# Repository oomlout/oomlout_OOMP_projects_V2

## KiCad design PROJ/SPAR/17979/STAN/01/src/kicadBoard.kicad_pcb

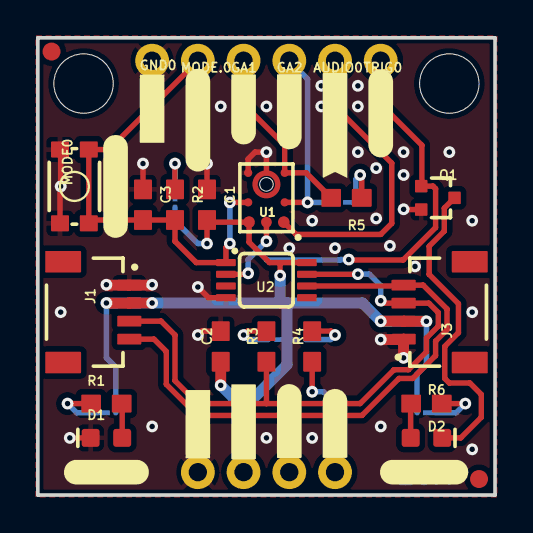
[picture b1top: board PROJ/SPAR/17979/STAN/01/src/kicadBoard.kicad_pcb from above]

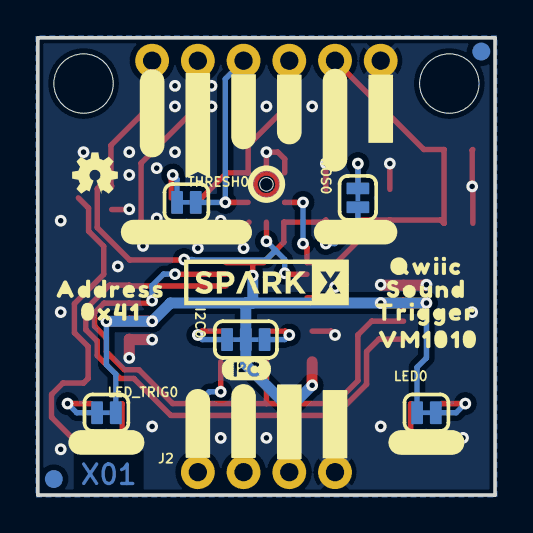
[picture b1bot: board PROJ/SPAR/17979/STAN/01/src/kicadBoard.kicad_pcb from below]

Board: 2 copper layers, 25.4 x 25.4 mm, 74 parts (31 on the bottom side), 18 nets.

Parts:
AUDIO0: 1X01_NO_SILK
C1, C3: 0.1uF; 0603
C2: 1.0uF; 0603
D1, D2: RED; LED-0603
FRAME1: FRAME-LETTER; CREATIVE_COMMONS
GA1, GA2: 1X01_NO_SILK
GND0: 1X01_NO_SILK
I2C0: JUMPER-SMT_3_2-NC_TRACE_SILK; SMT-JUMPER_3_2-NC_TRACE_SILK
J1, J3: Qwiic Right Angle; JST04_1MM_RA
J2: PTH; 1X04_NO_SILK
JP1, JP2, JP5, JP6: FIDUCIAL1X2; FIDUCIAL-1X2
JP3, JP4: STAND-OFF
LED0: SMT-JUMPER_2_NC_TRACE_SILK
LED_TRIG0: SMT-JUMPER_2_NC_TRACE_SILK
LOGO1: OSHW-LOGOMINI; OSHW-LOGO-MINI
LOGO2: SPECIAL_INSTRUCTIONS-ORDERING; ORDERING_INSTRUCTIONS
LOGO3: SPECIAL_INSTRUCTIONS-PRODUCTION; PRODUCTION_INSTRUCTIONS
MODE0: MOMENTARY-SWITCH-SPST-SMD-4.6X2.8MM; TACTILE_SWITCH_SMD_4.6X2.8MM
MODE.0: 1X01_NO_SILK
Q1: 310mA/60V/1.6Ω; SOT323
R1, R6: 1k; 0603
R2, R3, R4: 2.2k; 0603
R5: 20k; 0603
THRESH0: SMT-JUMPER_2_NC_TRACE_SILK
TRIG0: 1X01_NO_SILK
U1: VM1010
U2: PCA9536; MSOP8
U$1, U$3: #GA1#0
U$2: SPARKX-LOGO4; SPARKX-MEDIUM
U$4, U$5: #GA2#0
U$6, U$7: #AUDIO#0
U$8, U$9, U$25: #MODE#0
U$10: I_SUPER2_C-()-03
U$11, U$12, U$35: #TRIG#0
U$13: #PWR#0
U$14, U$36: #LED#0
U$15: #THRESH#0
U$16: #WOS#0
U$17, U$18, U$38, U$39: #GND#0
U$19, U$20: #3#3V#0
U$21, U$22: #SDA#0
U$23, U$24: #SCL#0
U$29: QWIIC0
U$30: SOUND0
U$31: TRIGGER0
U$32: VM10100
U$33: ADDRESS0
U$34: 0X410
WOS0: SMT-JUMPER_2_NC_TRACE_SILK

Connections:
3.3V: C1.1, C2.1, I2C0.2, J1.2, J2.2, J3.2, LED0.2, LED_TRIG0.2, U1.6, U2.8, WOS0.2
AUDIO: AUDIO0.1, U1.1
GA1: GA1.1, R5.1, U1.3
GA2: GA2.1, THRESH0.2, U1.2
GND: C1.2, C2.2, C3.2, D1.C, GND0.1, J1.1, J2.1, J3.1, MODE0.1, MODE0.2, Q1.2, U1.4, U1.8, U2.4
MODE: C3.1, MODE0.3, MODE0.4, MODE.0.1, R2.1, U1.5, U2.1
unnamed: I2C0.1, R4.2
unnamed: I2C0.3, R3.2
unnamed: D1.A, R1.1
unnamed: LED0.1, R1.2
unnamed: R2.2, WOS0.1
unnamed: R5.2, THRESH0.1
unnamed: D2.A, R6.1
unnamed: LED_TRIG0.1, R6.2
unnamed: D2.C, Q1.3
SCL: J1.4, J2.4, J3.4, R4.1, U2.6
SDA: J1.3, J2.3, J3.3, R3.1, U2.7
TRIG: Q1.1, TRIG0.1, U1.7, U2.2

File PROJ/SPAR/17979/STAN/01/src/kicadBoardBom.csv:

"Id";"Designator";"Package";"Quantity";"Designation";"Supplier and ref";
1;"U$13";"#PWR#0";1;"";;;
2;"U2";"MSOP8";1;"PCA9536";;;
3;"MODE0";"TACTILE_SWITCH_SMD_4.6X2.8MM";1;"MOMENTARY-SWITCH-SPST-SMD-4.6X2.8MM";;;
4;"U$6,U$7";"#AUDIO#0";2;"";;;
5;"JP6,JP2,JP5,JP1";"FIDUCIAL-1X2";4;"FIDUCIAL1X2";;;
6;"R6,R1";"0603";2;"1k";;;
7;"U$21,U$22";"#SDA#0";2;"";;;
8;"FRAME1";"CREATIVE_COMMONS";1;"FRAME-LETTER";;;
9;"R4,R2,R3";"0603";3;"2.2k";;;
10;"AUDIO0,MODE.0,GA1,TRIG0,GND0,GA2";"1X01_NO_SILK";6;"";;;
11;"C3,C1";"0603";2;"0.1uF";;;
12;"U$19,U$20";"#3#3V#0";2;"";;;
13;"J1,J3";"JST04_1MM_RA";2;"Qwiic Right Angle";;;
14;"U$8,U$25,U$9";"#MODE#0";3;"";;;
15;"U$39,U$17,U$18,U$38";"#GND#0";4;"";;;
16;"LOGO2";"ORDERING_INSTRUCTIONS";1;"SPECIAL_INSTRUCTIONS-ORDERING";;;
17;"R5";"0603";1;"20k";;;
18;"U$23,U$24";"#SCL#0";2;"";;;
19;"U1";"VM1010";1;"VM1010";;;
20;"U$11,U$35,U$12";"#TRIG#0";3;"";;;
21;"U$1,U$3";"#GA1#0";2;"";;;
22;"JP4,JP3";"STAND-OFF";2;"STAND-OFF";;;
23;"D2,D1";"LED-0603";2;"RED";;;
24;"U$4,U$5";"#GA2#0";2;"";;;
25;"C2";"0603";1;"1.0uF";;;
26;"LOGO3";"PRODUCTION_INSTRUCTIONS";1;"SPECIAL_INSTRUCTIONS-PRODUCTION";;;
27;"Q1";"SOT323";1;"310mA/60V/1.6Ω";;;
28;"U$30";"SOUND0";1;"";;;
29;"U$33";"ADDRESS0";1;"";;;
30;"WOS0,LED_TRIG0,LED0,THRESH0";"SMT-JUMPER_2_NC_TRACE_SILK";4;"";;;
31;"U$15";"#THRESH#0";1;"";;;
32;"U$34";"0X410";1;"";;;
33;"J2";"1X04_NO_SILK";1;"PTH";;;
34;"I2C0";"SMT-JUMPER_3_2-NC_TRACE_SILK";1;"JUMPER-SMT_3_2-NC_TRACE_SILK";;;
35;"U$14,U$36";"#LED#0";2;"";;;
36;"U$16";"#WOS#0";1;"";;;
37;"LOGO1";"OSHW-LOGO-MINI";1;"OSHW-LOGOMINI";;;
38;"U$32";"VM10100";1;"";;;
39;"U$31";"TRIGGER0";1;"";;;
40;"U$29";"QWIIC0";1;"";;;
41;"U$2";"SPARKX-MEDIUM";1;"SPARKX-LOGO4";;;
42;"U$10";"I_SUPER2_C-()-03";1;"";;;

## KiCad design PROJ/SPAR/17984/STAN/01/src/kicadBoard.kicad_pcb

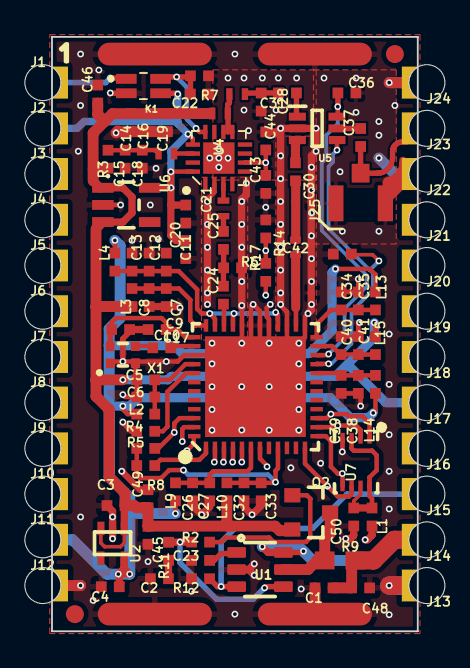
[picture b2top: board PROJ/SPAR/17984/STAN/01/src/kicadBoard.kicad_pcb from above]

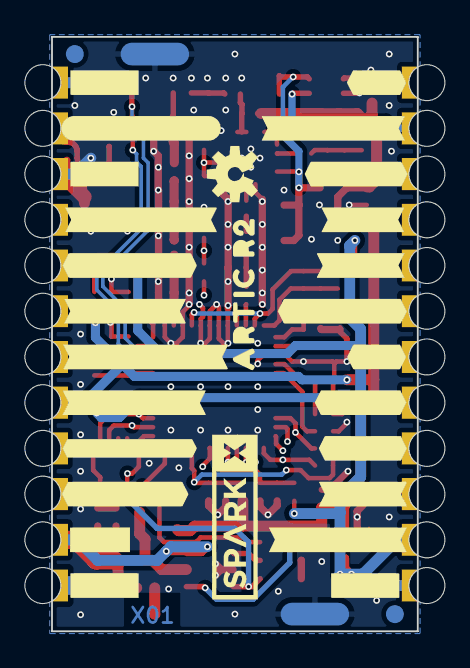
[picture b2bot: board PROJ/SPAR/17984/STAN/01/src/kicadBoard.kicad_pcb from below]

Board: 4 copper layers, 20.3 x 33.0 mm, 146 parts (29 on the bottom side), 57 nets.

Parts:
C1, C15, C16, C20, C44, C45: 2.2uF; 0402-TIGHT
C2: 10nF; 0402-TIGHT
C3, C4, C9, C12, C23, C46: 1.0uF; 0402-TIGHT
C5, C7, C18, C27, C33, C34, C39, C40: 22pF; 0402-TIGHT
C6, C8, C26, C32, C35, C38, C41, C48, C49, C50: 0.1uF; 0402-TIGHT
C10: 47nF; 0402-TIGHT
C11, C19, C21, C22, C24, C25, C30, C31, C36, C37, C42, C43: 100pF; 0402-TIGHT
C13, C14: 10uF; 0402-TIGHT
C17: 1.0nF; 0402-TIGHT
C28: 9.1pF; 0402-TIGHT
C29: 2.4 pF; 0402_MURATA
FD1, FD2, FD3, FD4: FIDUCIAL1X2; FIDUCIAL-1X2
FRAME1: FRAME-LEDGER; CREATIVE_COMMONS
J1, J2, J3, J4, J5, J6, J7, J8, J9, J10, J11, J12, J13, J14, J15, J16, J17, J18, J19, J20, J21, J22, J23, J24: CONN_01_CASTELLATED_4LAYER
J25: U.FL; U.FL_REDUCED_FOOTPRINT
K1: TLP3475R; TLP3475RTPF
L1, L2, L3, L4, L9, L10, L13, L14, L15: 30Ω; 0402-TIGHT
L5: 15nH; 0402_COILCRAFT
L6: 27nH; 0402_COILCRAFT
L7: 18nH; 0402_COILCRAFT
L8: 12nH; 0402_COILCRAFT
L11: 30nH; 0402_COILCRAFT
L12: 51nH; 0402_COILCRAFT
LOGO1: SPECIAL_INSTRUCTIONS-ORDERING; ORDERING_INSTRUCTIONS
LOGO3: OSHW-LOGOS; OSHW-LOGO-S
Q2: 5.8A/30V/35mΩ; SOT23-3
R2, R11: 100; 0402-TIGHT
R3: 3.9; 0402-TIGHT
R4: 33k; 0402-TIGHT
R5, R8: 100k; 0402-TIGHT
R6: 220; 0402-TIGHT
R7, R12: 10k; 0402-TIGHT
R9: 0.1; 0603
R14: 470; 0402-TIGHT
R17: 47; 0402-TIGHT
SCREEN0: IOTA_SCREENING_CANSTRAIGHT_SLOTS; IOTA_CAN_STRAIGHT_SLOTS
SPARKX2: SPARKX-LOGO4; SPARKX-MEDIUM
U1: ADM4210_1TSOT6; TSOT6
U2: 1.8V/100mA; SC70
U3: ARTIC_R2; QFN-48
U4: RFPA0133; QFN50P300X300X86-17N
U5: AS179-92LF; SOT65P220X100-6N
U6: 3.0V; SOT23-5
U7: SST25VF020BUSON; USON_3X2MM
U$1, U$3, U$4, U$5: #GND#0
U$2: 10
U$6: #PWR_EN#0
U$7: #VIN#0
U$8: #FLASH_PWR#0
U$9: #FLSH_SCLK#0
U$10: #FLSH_SI#0
U$11: #FLSH_SO#0
U$12: #FLSH_CEN#0
U$13: #3#3V_OUT#0
U$14: #ANTENNA#0
U$15: #G8#0
U$16: #3#0V_OUT#0
U$17: #BOOT#0
U$18: #INT1#0
U$19: #INT2#0
U$20: #RESETB#0
U$21: #CS#0
U$22: #SCLK#0
U$23: #COPI#0
U$24: #CIPO#0
U$25: #1#8V_OUT#0
U$26: ARTIC_R20
X1: CRYSTAL-TCXO-26MHZ; CRYSTAL-TCXO-SMD-1.65X1.25

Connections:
1.8V: C4.1, J11.1, L2.2, L4.2, L9.2, L13.2, L14.2, U2.5
ANTENNA: C37.1, J23.1, J25.FEED
BOOT: J3.1, R5.1, U3.46
CIPO: J10.1, U3.5
COPI: J9.1, U3.4
CS: J7.1, U3.2
FLASH_PWR: J16.1, L1.2
FLASH_VCC: C50.1, L1.1, U7.3, U7.7, U7.8
FLSH_CEN: J21.1, U3.15, U7.1
FLSH_SCLK: J18.1, U3.12, U7.6
FLSH_SI: J19.1, U3.13, U7.5
FLSH_SO: J20.1, U3.14, U7.2
G8: J1.1, K1.1
GND: C1.2, C2.2, C3.2, C4.2, C5.2, C6.2, C7.2, C8.2, C9.2, C10.2, C11.2, C12.2, C13.2, C14.2, C15.2, C16.2, C18.2, C19.2, C20.1, C21.1, C22.1, C23.2, C26.2, C27.2, C28.1, C32.2, C33.2, C34.2, C35.2, C36.2, C38.2, C39.2, C40.2, C41.2, C42.2, C43.1, C44.2, C45.2, C46.2, C48.2, C49.2, C50.2, J12.1, J13.1, J22.1, J24.1, J25.1, J25.2, K1.2, L11.P$1, L12.P$1, R4.2, R6.1, R7.2, R12.2, R14.1, SCREEN0.1-1, SCREEN0.1-16, SCREEN0.2, SCREEN0.3-1, SCREEN0.3-16, SCREEN0.4, U1.2, U2.2, U3.25, U3.27, U3.29, U3.30, U3.31, U3.32, U3.39, U3.GND, U4.2, U4.EDAP, U5.2, U6.2, U7.4, X1.1, X1.2
INT1: J4.1, U3.47
INT2: J5.1, U3.48
unnamed: Q2.3, R9.1, U1.5
unnamed: Q2.1, R2.1
unnamed: R2.2, R11.1, U1.4
unnamed: C34.1, C35.1, L13.1, U3.24
unnamed: C40.1, C41.1, L15.1, U3.23
unnamed: C2.1, R11.2
unnamed: C23.1, U1.1
unnamed: C26.1, C27.1, L9.1, U3.6
unnamed: C32.1, C33.1, L10.1, R5.2, R8.1, U3.9
unnamed: C11.1, C12.1, C13.1, L4.1, U3.28, U3.33, U3.35
unnamed: C7.1, C8.1, L3.1, U3.36
unnamed: R4.1, U3.41
unnamed: C5.1, C6.1, L2.1, U3.40
unnamed: C9.1, C10.1, U3.37, X1.4
unnamed: C17.1, X1.3
unnamed: C17.2, U3.38
unnamed: C24.1, U3.34
unnamed: C24.2, C25.1, R6.2
unnamed: L5.P$2, U4.14
unnamed: C15.1, C18.1, L5.P$1, R3.1
unnamed: C29.P$1, L11.P$2, U3.26
unnamed: C25.2, L7.P$1
unnamed: L7.P$2, U4.3
unnamed: L6.P$2, L8.P$1, U4.9, U4.10
unnamed: C31.1, U5.1
unnamed: C30.1, U5.3
unnamed: C37.2, U5.5
unnamed: C38.1, C39.1, L14.1, U3.20
PA_PD: R17.1, U3.7
PD: C43.2, C44.1, R14.2, R17.2, U4.6
PWR_EN: J15.1, R12.1, U1.3
RESETB: J6.1, R8.2, U3.1
RFG8: C22.2, K1.4, R7.1, U4.12
RF_RX: C29.P$2, C30.2, L12.P$2
RF_TX: C28.2, C31.2, L8.P$2
RXSW: C36.1, U3.22, U5.6
SCLK: J8.1, U3.3
TXSW: C42.1, U3.21, U5.4
VDD: C3.1, C14.1, C16.1, C19.1, C45.1, C46.1, C49.1, J17.1, L3.2, L6.P$1, L10.2, L15.2, Q2.2, R3.2, U2.1, U2.3, U6.1, U6.3
VIN: C1.1, C48.1, J14.1, R9.2, U1.6
VREF1: C20.2, C21.2, J2.1, K1.3, U4.13, U4.16, U6.5

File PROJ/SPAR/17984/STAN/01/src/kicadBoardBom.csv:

"Id";"Designator";"Package";"Quantity";"Designation";"Supplier and ref";
1;"J20,J18,J9,J11,J10,J2,J6,J17,J1,J16,J5,J19,J24,J15,J4,J23,J13,J8,J22,J3,J14,J12,J7,J21";"CONN_01_CASTELLATED_4LAYER";24;"";;;
2;"C18,C27,C33,C5,C34,C39,C40,C7";"0402-TIGHT";8;"22pF";;;
3;"R4";"0402-TIGHT";1;"33k";;;
4;"K1";"TLP3475RTPF";1;"TLP3475R";;;
5;"C43,C42,C21,C37,C11,C31,C25,C19,C30,C22,C36,C24";"0402-TIGHT";12;"100pF";;;
6;"C29";"0402_MURATA";1;"2.4 pF";;;
7;"C13,C14";"0402-TIGHT";2;"10uF";;;
8;"C4,C9,C12,C46,C23,C3";"0402-TIGHT";6;"1.0uF";;;
9;"L6";"0402_COILCRAFT";1;"27nH";;;
10;"C1,C20,C44,C45,C16,C15";"0402-TIGHT";6;"2.2uF";;;
11;"FD1,FD3,FD4,FD2";"FIDUCIAL-1X2";4;"FIDUCIAL1X2";;;
12;"L10,L14,L9,L13,L3,L15,L1,L4,L2";"0402-TIGHT";9;"30Ω";;;
13;"L7";"0402_COILCRAFT";1;"18nH";;;
14;"R14";"0402-TIGHT";1;"470";;;
15;"C2";"0402-TIGHT";1;"10nF";;;
16;"Q2";"SOT23-3";1;"5.8A/30V/35mΩ";;;
17;"R8,R5";"0402-TIGHT";2;"100k";;;
18;"R3";"0402-TIGHT";1;"3.9";;;
19;"L5";"0402_COILCRAFT";1;"15nH";;;
20;"C8,C50,C32,C35,C38,C49,C41,C48,C26,C6";"0402-TIGHT";10;"0.1uF";;;
21;"R12,R7";"0402-TIGHT";2;"10k";;;
22;"U5";"SOT65P220X100-6N";1;"AS179-92LF";;;
23;"U4";"QFN50P300X300X86-17N";1;"RFPA0133";;;
24;"X1";"CRYSTAL-TCXO-SMD-1.65X1.25";1;"CRYSTAL-TCXO-26MHZ";;;
25;"U2";"SC70";1;"1.8V/100mA";;;
26;"R11,R2";"0402-TIGHT";2;"100";;;
27;"L11";"0402_COILCRAFT";1;"30nH";;;
28;"SCREEN0";"IOTA_CAN_STRAIGHT_SLOTS";1;"IOTA_SCREENING_CANSTRAIGHT_SLOTS";;;
29;"U7";"USON_3X2MM";1;"SST25VF020BUSON";;;
30;"U1";"TSOT6";1;"ADM4210_1TSOT6";;;
31;"C10";"0402-TIGHT";1;"47nF";;;
32;"L8";"0402_COILCRAFT";1;"12nH";;;
33;"LOGO1";"ORDERING_INSTRUCTIONS";1;"SPECIAL_INSTRUCTIONS-ORDERING";;;
34;"U$2";"10";1;"";;;
35;"J25";"U.FL_REDUCED_FOOTPRINT";1;"U.FL";;;
36;"R6";"0402-TIGHT";1;"220";;;
37;"C17";"0402-TIGHT";1;"1.0nF";;;
38;"C28";"0402-TIGHT";1;"9.1pF";;;
39;"R17";"0402-TIGHT";1;"47";;;
40;"U3";"QFN-48";1;"ARTIC_R2";;;
41;"L12";"0402_COILCRAFT";1;"51nH";;;
42;"U6";"SOT23-5";1;"3.0V";;;
43;"FRAME1";"CREATIVE_COMMONS";1;"FRAME-LEDGER";;;
44;"R9";"0603";1;"0.1";;;
45;"U$14";"#ANTENNA#0";1;"";;;
46;"U$21";"#CS#0";1;"";;;
47;"U$7";"#VIN#0";1;"";;;
48;"U$22";"#SCLK#0";1;"";;;
49;"LOGO3";"OSHW-LOGO-S";1;"OSHW-LOGOS";;;
50;"U$3,U$4,U$5,U$1";"#GND#0";4;"";;;
51;"U$8";"#FLASH_PWR#0";1;"";;;
52;"U$6";"#PWR_EN#0";1;"";;;
53;"U$12";"#FLSH_CEN#0";1;"";;;
54;"U$26";"ARTIC_R20";1;"";;;
55;"U$24";"#CIPO#0";1;"";;;
56;"U$16";"#3#0V_OUT#0";1;"";;;
57;"U$20";"#RESETB#0";1;"";;;
58;"U$23";"#COPI#0";1;"";;;
59;"U$11";"#FLSH_SO#0";1;"";;;
60;"U$13";"#3#3V_OUT#0";1;"";;;
61;"U$18";"#INT1#0";1;"";;;
62;"U$10";"#FLSH_SI#0";1;"";;;
63;"U$9";"#FLSH_SCLK#0";1;"";;;
64;"U$25";"#1#8V_OUT#0";1;"";;;
65;"U$19";"#INT2#0";1;"";;;
66;"U$17";"#BOOT#0";1;"";;;
67;"U$15";"#G8#0";1;"";;;
68;"SPARKX2";"SPARKX-MEDIUM";1;"SPARKX-LOGO4";;;

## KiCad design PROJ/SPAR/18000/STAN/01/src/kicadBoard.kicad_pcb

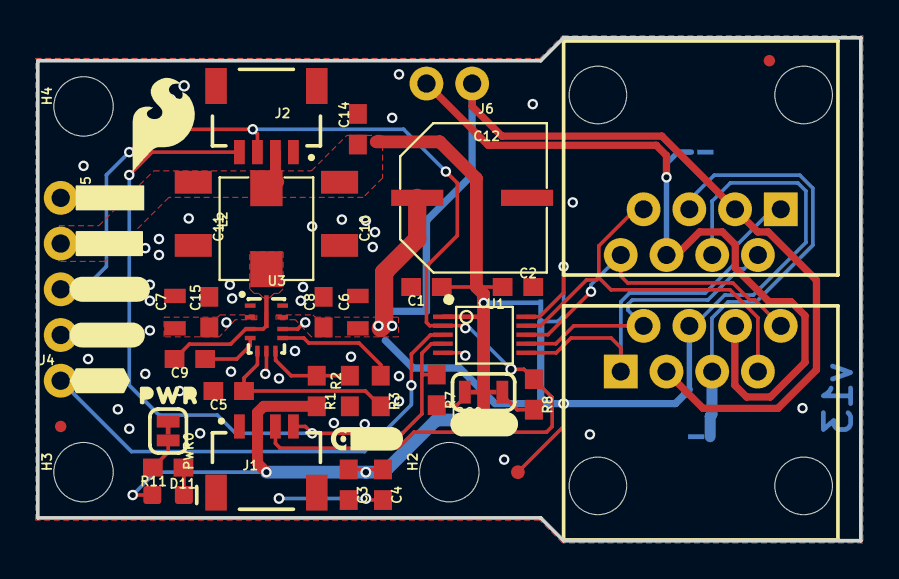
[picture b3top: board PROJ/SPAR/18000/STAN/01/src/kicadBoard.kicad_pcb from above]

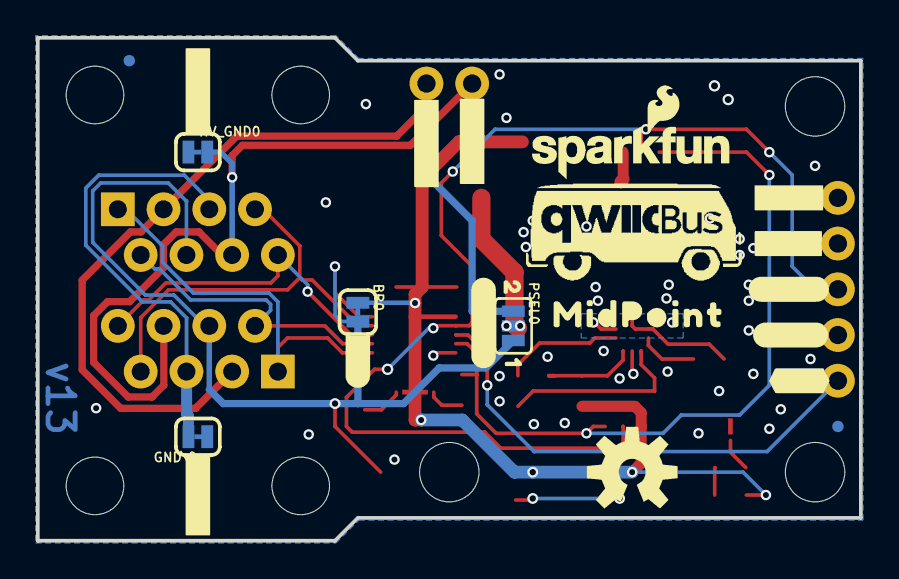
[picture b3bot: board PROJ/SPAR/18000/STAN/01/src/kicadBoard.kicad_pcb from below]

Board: 2 copper layers, 45.7 x 27.9 mm, 73 parts (23 on the bottom side), 23 nets.

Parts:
BP0: JUMPER-SMT_2_NC_TRACE_SILK; SMT-JUMPER_2_NC_TRACE_SILK
C1, C2, C9, C14: 0.1uF; 0603
C3, C4, C5: 1.0uF; 0603
C6, C7: 4.7uF; 0805
C8, C15: 0.22uF; 0603
C10, C11: 22uF; 1210
C12: 100uF; 8X10.5
D11: RED; LED-0603
FD1, FD2, FD3, FD4: FIDUCIALUFIDUCIAL; FIDUCIAL-MICRO
FRAME1: FRAME-LETTER; CREATIVE_COMMONS
GND\0: JUMPER-SMT_2_NC_TRACE_SILK; SMT-JUMPER_2_NC_TRACE_SILK
H2, H3, H4: STAND-OFF
HV_GND0: JUMPER-SMT_2_NC_TRACE_SILK; SMT-JUMPER_2_NC_TRACE_SILK
I2C0: JUMPER-SMT_3_2-NC_TRACE_SILK; SMT-JUMPER_3_2-NC_TRACE_SILK
J1, J2: QWIIC; JST04_1MM_RA
J3, J7: RJ45; RJ45-8
J4: 1X01_NO_SILK
J5: 1X04_NO_SILK
J6: 1X02_NO_SILK
L2: 2.2uH; INDUCTOR_5X5MM
LOGO1: OSHW-LOGOM; OSHW-LOGO-M
LOGO3: SFE_LOGO_FLAME.2_INCH; SFE_LOGO_FLAME_.2
LOGO4: SFE_LOGO_NAME_FLAME.1_INCH; SFE_LOGO_NAME_FLAME_.1
PSEL0: JUMPER-SMT_3_NO_SILK; SMT-JUMPER_3_NO_SILK
PWR0: JUMPER-SMT_2_NC_TRACE_SILK; SMT-JUMPER_2_NC_TRACE_SILK
R1, R3: 100k; 0603
R2: 43k; 0603
R7, R8: 4.7k; 0603
R11: 1k; 0603
TP1: TEST-POINT3; PAD.03X.03
U1: PCA9615; TSSOP10
U3: LMR33630; VQFN-HR-12
U$1, U$7: #GND#0
U$2, U$8: #3V3#0
U$3, U$9: #SDA#0
U$4, U$10: #SCL#0
U$5: #BP#0
U$6, U$12: #EN#0
U$11, U$24: #GND2#0
U$13: #I2C#0
U$14: #GND1#0
U$15: QWIICBUS#WORKING#LOGO#JPG
U$16: #VCC2#0
U$17: #PSEL#0
U$18: 10
U$19: 20
U$20: ORDERING_INSTRUCTIONS
U$22: QWIIC_4MM
U$23: PWR0
U$30: MIDPOINT0

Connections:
3.3V: BP0.1, C1.1, C2.1, C3.1, C4.1, C10.1, C11.1, C14.1, D11.A, I2C0.2, J1.2, J2.2, J5.2, L2.P$2, R1.2, U1.1
BLUE_N: GND\0.2, J3.5, J7.5
DSCL_N: J3.1, J7.1, U1.6
DSCL_P: J3.2, J7.2, U1.7
DSDA_N: J3.7, J7.7, U1.9
DSDA_P: J3.8, J7.8, U1.8
EN: J4.1, U1.3
GND: C1.2, C2.2, C3.2, C4.2, C5.2, C6.2, C7.2, C8.2, C10.2, C11.2, C12.-, C14.2, C15.2, GND\0.1, HV_GND0.1, J1.1, J2.1, J5.1, PWR0.1, R2.1, U1.5, U3.1, U3.6, U3.11
GRN_N: HV_GND0.2, J3.6, J6.2, J7.6
unnamed: C9.1, U3.4
unnamed: I2C0.1, R8.2
unnamed: I2C0.3, R7.2
unnamed: R1.1, R2.2, U3.7
unnamed: R3.1, U3.8
unnamed: C5.1, R3.2, U3.5
unnamed: D11.C, R11.1
unnamed: PWR0.2, R11.2
SCL: J1.4, J2.4, J5.4, R7.1, U1.4
SDA: J1.3, J2.3, J5.3, R8.1, U1.2
SW: C9.2, L2.P$1, U3.3, U3.12
VCC_1: BP0.2, J3.4, J7.4, PSEL0.3, TP1.P$1, U1.10
VCC_2: J3.3, J6.1, J7.3, PSEL0.1
VREG_IN: C6.1, C7.1, C8.1, C12.+, C15.1, PSEL0.2, U3.2, U3.9, U3.10

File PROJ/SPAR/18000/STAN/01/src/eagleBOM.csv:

"Part";"Value";"Device";"Package";"Description";"DESIGNER";"PROD_ID";"REV";"SF_ID";"VALUE";
"BP";"JUMPER-SMT_2_NC_TRACE_SILK";"JUMPER-SMT_2_NC_TRACE_SILK";"SMT-JUMPER_2_NC_TRACE_SILK";"Normally closed trace jumper";"";"";"";"";"";
"C1";"0.1uF";"0.1UF-0603-25V-(+80/-20%)";"0603";"0.1µF ceramic capacitors";"";"CAP-00810";"";"";"0.1uF";
"C2";"0.1uF";"0.1UF-0603-25V-(+80/-20%)";"0603";"0.1µF ceramic capacitors";"";"CAP-00810";"";"";"0.1uF";
"C3";"1.0uF";"1.0UF-0603-16V-10%";"0603";"1µF ceramic capacitors";"";"CAP-00868";"";"";"1.0uF";
"C4";"1.0uF";"1.0UF-0603-16V-10%";"0603";"1µF ceramic capacitors";"";"CAP-00868";"";"";"1.0uF";
"C5";"1.0uF";"1.0UF-0603-16V-10%";"0603";"1µF ceramic capacitors";"";"CAP-00868";"";"";"1.0uF";
"C6";"4.7uF";"4.7UF-0805-50V-(10%)";"0805";"4.7µF ceramic capacitors";"";"CAP-15457";"";"";"4.7uF";
"C7";"4.7uF";"4.7UF-0805-50V-(10%)";"0805";"4.7µF ceramic capacitors";"";"CAP-15457";"";"";"4.7uF";
"C8";"0.22uF";"0.22UF-0603-50V-10%";"0603";"0.22µF ceramic capacitors";"";"CAP-15456";"";"";"0.22uF";
"C9";"0.1uF";"0.1UF-0603-100V-10%";"0603";"0.1µF ceramic capacitors";"";"CAP-08390";"";"";"0.1uF";
"C10";"22uF";"22UF-1210-16V-20%";"1210";"22µF ceramic capacitors";"";"CAP-10381";"";"";"22uF";
"C11";"22uF";"22UF-1210-16V-20%";"1210";"22µF ceramic capacitors";"";"CAP-10381";"";"";"22uF";
"C12";"100uF";"100UF-POLAR-8X10.5-50V";"8X10.5";"100µF polarized capacitors";"";"CAP-15455";"";"";"100uF";
"C14";"0.1uF";"0.1UF-0603-100V-10%";"0603";"0.1µF ceramic capacitors";"";"CAP-08390";"";"";"0.1uF";
"C15";"0.22uF";"0.22UF-0603-50V-10%";"0603";"0.22µF ceramic capacitors";"";"CAP-15456";"";"";"0.22uF";
"D11";"RED";"LED-RED0603";"LED-0603";"Red SMD LED";"";"DIO-00819";"";"";"RED";
"FD1";"FIDUCIALUFIDUCIAL";"FIDUCIALUFIDUCIAL";"FIDUCIAL-MICRO";"Fiducial Alignment Points";"";"";"";"";"";
"FD2";"FIDUCIALUFIDUCIAL";"FIDUCIALUFIDUCIAL";"FIDUCIAL-MICRO";"Fiducial Alignment Points";"";"";"";"";"";
"FD3";"FIDUCIALUFIDUCIAL";"FIDUCIALUFIDUCIAL";"FIDUCIAL-MICRO";"Fiducial Alignment Points";"";"";"";"";"";
"FD4";"FIDUCIALUFIDUCIAL";"FIDUCIALUFIDUCIAL";"FIDUCIAL-MICRO";"Fiducial Alignment Points";"";"";"";"";"";
"FRAME1";"FRAME-LETTER";"FRAME-LETTER";"CREATIVE_COMMONS";"Schematic Frame - Letter";"";"";"";"";"";
"GND\";"JUMPER-SMT_2_NC_TRACE_SILK";"JUMPER-SMT_2_NC_TRACE_SILK";"SMT-JUMPER_2_NC_TRACE_SILK";"Normally closed trace jumper";"";"";"";"";"";
"H2";"STAND-OFF";"STAND-OFF";"STAND-OFF";"Stand Off";"";"";"";"";"";
"H3";"STAND-OFF";"STAND-OFF";"STAND-OFF";"Stand Off";"";"";"";"";"";
"H4";"STAND-OFF";"STAND-OFF";"STAND-OFF";"Stand Off";"";"";"";"";"";
"HV_GND";"JUMPER-SMT_2_NC_TRACE_SILK";"JUMPER-SMT_2_NC_TRACE_SILK";"SMT-JUMPER_2_NC_TRACE_SILK";"Normally closed trace jumper";"";"";"";"";"";
"I2C";"JUMPER-SMT_3_2-NC_TRACE_SILK";"JUMPER-SMT_3_2-NC_TRACE_SILK";"SMT-JUMPER_3_2-NC_TRACE_SILK";"Normally closed trace jumper (2 of 2 connections)";"";"";"";"";"";
"J1";"QWIIC";"QWIIC_CONNECTORJS-1MM";"JST04_1MM_RA";"SparkFun I2C Standard Qwiic Connector";"";"CONN-13694";"";"";"QWIIC_RIGHT_ANGLE";
"J2";"QWIIC";"QWIIC_CONNECTORJS-1MM";"JST04_1MM_RA";"SparkFun I2C Standard Qwiic Connector";"";"CONN-13694";"";"";"QWIIC_RIGHT_ANGLE";
"J3";"RJ45";"RJ45-8";"RJ45-8";"RJ45 Jack - 8 pin";"";"CONN-08506";"";"PRT-00643";"RJ45";
"J4";"";"CONN_01PTH_NO_SILK_YES_STOP";"1X01_NO_SILK";"Single connection point. Often used as Generic Header-pin footprint for 0.1 inch spaced/style header connections";"";"";"";"";"";
"J5";"";"CONN_041X04_NO_SILK";"1X04_NO_SILK";"Multi connection point. Often used as Generic Header-pin footprint for 0.1 inch spaced/style header connections";"";"CONN-09696";"";"";"";
"J6";"";"CONN_021X02_NO_SILK";"1X02_NO_SILK";"Multi connection point. Often used as Generic Header-pin footprint for 0.1 inch spaced/style header connections";"";"";"";"";"";
"J7";"RJ45";"RJ45-8";"RJ45-8";"RJ45 Jack - 8 pin";"";"CONN-08506";"";"PRT-00643";"RJ45";
"L2";"2.2uH";"2.2μH_SHIELDED_INDUCTOR_5X5";"INDUCTOR_5X5MM";"Murata 2.2uH Inductor";"";"NDUC-15453";"";"";"2.2uH";
"LOGO1";"OSHW-LOGOM";"OSHW-LOGOM";"OSHW-LOGO-M";"Open-Source Hardware (OSHW) Logo";"";"";"";"";"";
"LOGO3";"SFE_LOGO_FLAME.2_INCH";"SFE_LOGO_FLAME.2_INCH";"SFE_LOGO_FLAME_.2";"SparkFun Flame Logo";"";"";"";"";"";
"LOGO4";"SFE_LOGO_NAME_FLAME.1_INCH";"SFE_LOGO_NAME_FLAME.1_INCH";"SFE_LOGO_NAME_FLAME_.1";"SparkFun Font Logo w/ Flame";"";"";"";"";"";
"PSEL";"JUMPER-SMT_3_NO_SILK";"JUMPER-SMT_3_NO_SILK";"SMT-JUMPER_3_NO_SILK";"Normally open jumper";"";"";"";"";"";
"PWR";"JUMPER-SMT_2_NC_TRACE_SILK";"JUMPER-SMT_2_NC_TRACE_SILK";"SMT-JUMPER_2_NC_TRACE_SILK";"Normally closed trace jumper";"";"";"";"";"";
"R1";"100k";"100KOHM-0603-1/10W-1%";"0603";"100kΩ resistor";"";"RES-07828";"";"";"100k";
"R2";"43k";"43KOHM-0603-1/10W-1%";"0603";"43kΩ resistor";"";"RES-07858";"";"";"43k";
"R3";"100k";"100KOHM-0603-1/10W-1%";"0603";"100kΩ resistor";"";"RES-07828";"";"";"100k";
"R7";"4.7k";"4.7KOHM-0603-1/10W-1%";"0603";"4.7kΩ resistor";"";"RES-07857";"";"";"4.7k";
"R8";"4.7k";"4.7KOHM-0603-1/10W-1%";"0603";"4.7kΩ resistor";"";"RES-07857";"";"";"4.7k";
"R11";"1k";"1KOHM-0603-1/10W-1%";"0603";"1kΩ resistor";"";"RES-07856";"";"";"1k";
"TP1";"TEST-POINT3";"TEST-POINT3";"PAD.03X.03";"SparkFun Test Points";"";"";"";"";"";
"U1";"PCA9615";"PCA9615";"TSSOP10";"Differential I2C Bus Buffer";"";"IC-13899";"";"";"";
"U3";"LMR33630";"LMR33630";"VQFN-HR-12";"Texas Instruments LMR33630 3.8V-36V 3A Regulator";"";"VREG-15445";"";"";"LMR33630";

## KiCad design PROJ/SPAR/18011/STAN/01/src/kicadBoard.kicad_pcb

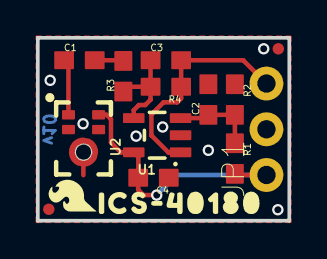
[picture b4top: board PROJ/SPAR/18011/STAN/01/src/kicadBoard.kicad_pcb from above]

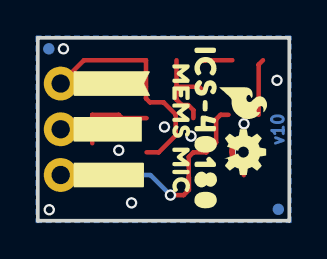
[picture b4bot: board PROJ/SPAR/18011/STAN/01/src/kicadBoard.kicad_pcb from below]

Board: 2 copper layers, 14.0 x 10.2 mm, 25 parts (9 on the bottom side), 7 nets.

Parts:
C1: 4.7uF; 0603
C2: 1.0uF; 0603
C3: 27pF; 0603
C4: 0.1uF; 0603
FD1, FD2, FD3, FD4: FIDUCIALUFIDUCIAL; FIDUCIAL-MICRO
FRAME2: FRAME-LETTER; CREATIVE_COMMONS
JP1: 1X03_NO_SILK
LOGO1, LOGO3: SFE_LOGO_FLAME.1_INCH; SFE_LOGO_FLAME_.1
LOGO2: OSHW-LOGOMINI; OSHW-LOGO-MINI
R1, R2: 10k; 0603
R3: 4.7k; 0603
R4: 300k; 0603
U1: OPA344; SOT23-5
U2: ICS40180
U$1, U$6: ICS#401800
U$2: MEMS_MIC0
U$3: #GND#0
U$4: #VCC#0
U$5: #AUD#0

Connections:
AUD: C3.2, JP1.3, R4.1, U1.1
GND: C2.2, C4.1, JP1.2, R2.1, U1.2, U2.2, U2.3, U2.4
unnamed: C1.1, U2.1
unnamed: C3.1, R3.1, R4.2, U1.4
unnamed: C1.2, R3.2
unnamed: C2.1, R1.1, R2.2, U1.3
VCC: C4.2, JP1.1, R1.2, U1.5, U2.5

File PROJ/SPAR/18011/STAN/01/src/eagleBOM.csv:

"Part";"Value";"Device";"Package";"Description";"DESIGNER";"PROD_ID";"REV";"VALUE";
"C1";"4.7uF";"4.7UF-0603-6.3V-(10%)";"0603";"4.7µF ceramic capacitors";"";"CAP-08280";"";"4.7uF";
"C2";"1.0uF";"1.0UF-0603-16V-10%";"0603";"1µF ceramic capacitors";"";"CAP-00868";"";"1.0uF";
"C3";"27pF";"27PF-0603-50V-5%";"0603";"27pF ceramic capacitors";"";"CAP-09989";"";"27pF";
"C4";"0.1uF";"0.1UF-0603-25V-(+80/-20%)";"0603";"0.1µF ceramic capacitors";"";"CAP-00810";"";"0.1uF";
"FD1";"FIDUCIALUFIDUCIAL";"FIDUCIALUFIDUCIAL";"FIDUCIAL-MICRO";"Fiducial Alignment Points";"";"";"";"";
"FD2";"FIDUCIALUFIDUCIAL";"FIDUCIALUFIDUCIAL";"FIDUCIAL-MICRO";"Fiducial Alignment Points";"";"";"";"";
"FD3";"FIDUCIALUFIDUCIAL";"FIDUCIALUFIDUCIAL";"FIDUCIAL-MICRO";"Fiducial Alignment Points";"";"";"";"";
"FD4";"FIDUCIALUFIDUCIAL";"FIDUCIALUFIDUCIAL";"FIDUCIAL-MICRO";"Fiducial Alignment Points";"";"";"";"";
"FRAME2";"FRAME-LETTER";"FRAME-LETTER";"CREATIVE_COMMONS";"Schematic Frame - Letter";"";"";"";"";
"JP1";"";"CONN_031X03_NO_SILK";"1X03_NO_SILK";"Multi connection point. Often used as Generic Header-pin footprint for 0.1 inch spaced/style header connections";"";"";"";"";
"LOGO1";"SFE_LOGO_FLAME.1_INCH";"SFE_LOGO_FLAME.1_INCH";"SFE_LOGO_FLAME_.1";"SparkFun Flame Logo";"";"";"";"";
"LOGO2";"OSHW-LOGOMINI";"OSHW-LOGOMINI";"OSHW-LOGO-MINI";"Open-Source Hardware (OSHW) Logo";"";"";"";"";
"R1";"10k";"10KOHM-0603-1/10W-1%";"0603";"10kΩ resistor";"";"RES-00824";"";"10k";
"R2";"10k";"10KOHM-0603-1/10W-1%";"0603";"10kΩ resistor";"";"RES-00824";"";"10k";
"R3";"4.7k";"4.7KOHM-0603-1/10W-1%";"0603";"4.7kΩ resistor";"";"RES-07857";"";"4.7k";
"R4";"300k";"300KOHM-0603-1/10W-1%";"0603";"300kΩ resistor";"";"RES-10809";"";"300k";
"U1";"OPA344";"OPA344";"SOT23-5";"Single gate rail-to-rail output op-amp. Inputs extend 300mV past rails.";"";"IC-08251";"";"OPA344";
"U2";"ICS40180";"ICS40180";"ICS40180";"ICS-40180 - RF-Hardened, Low-Noise MEMs Microphone with Bottom Port and Analog Output";"";"IC-15819";"";"";

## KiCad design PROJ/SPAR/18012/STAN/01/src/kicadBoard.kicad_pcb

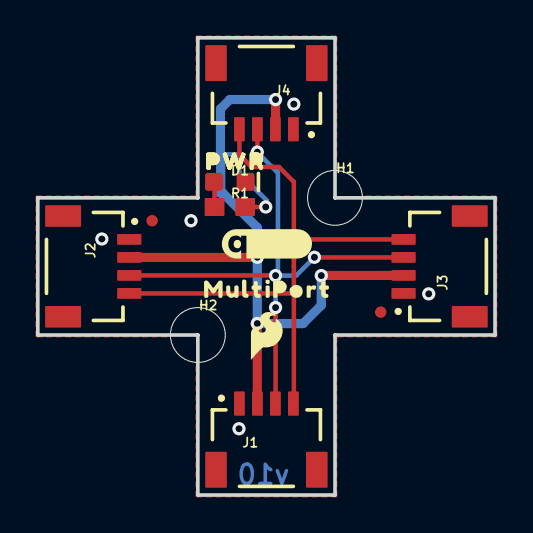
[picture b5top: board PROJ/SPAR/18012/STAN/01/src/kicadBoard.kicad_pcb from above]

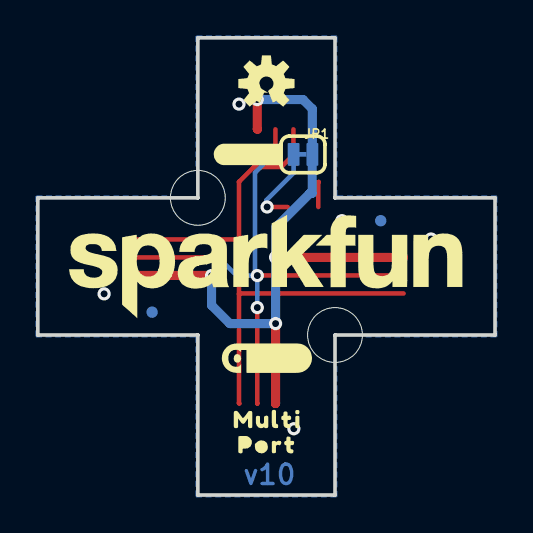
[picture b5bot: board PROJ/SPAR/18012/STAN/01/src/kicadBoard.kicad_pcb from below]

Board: 2 copper layers, 25.4 x 25.4 mm, 25 parts (9 on the bottom side), 6 nets.

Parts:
D1: RED; LED-0603
FD1, FD2, FD3, FD4: FIDUCIALUFIDUCIAL; FIDUCIAL-MICRO
FRAME1: FRAME-LETTER; CREATIVE_COMMONS
H1, H2: STAND-OFFTIGHT; STAND-OFF-TIGHT
J1, J2, J3, J4: QWIIC_RIGHT_ANGLE; JST04_1MM_RA
JP1: PWR_LED; SMT-JUMPER_2_NC_TRACE_SILK
LOGO1, LOGO2: QWIIC_LOGO_5MM; QWIIC_5MM
LOGO3: OSHW-LOGOS; OSHW-LOGO-S
LOGO4: SFE_LOGO_NAME.2_INCH; SFE_LOGO_NAME_.2
R1: 1k; 0603
U$1, U$9: PWR0
U$2: SFE_LOGO_FLAME_.1
U$4: MULTIPORT0
U$5: #PWR#0
U$11: MULTI0
U$13: PORT0

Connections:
3.3V: J1.2, J2.2, J3.2, J4.2, JP1.2
GND: D1.C, J1.1, J2.1, J3.1, J4.1
unnamed: D1.A, R1.1
unnamed: JP1.1, R1.2
SCL: J1.4, J2.4, J3.4, J4.4
SDA: J1.3, J2.3, J3.3, J4.3

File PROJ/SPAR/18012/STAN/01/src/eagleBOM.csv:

"Part";"Value";"Device";"Package";"Description";"DESIGNER";"PROD_ID";"REV";"VALUE";
"D1";"RED";"LED-RED0603";"LED-0603";"Red SMD LED";"";"DIO-00819";"";"RED";
"FD1";"FIDUCIALUFIDUCIAL";"FIDUCIALUFIDUCIAL";"FIDUCIAL-MICRO";"Fiducial Alignment Points";"";"";"";"";
"FD2";"FIDUCIALUFIDUCIAL";"FIDUCIALUFIDUCIAL";"FIDUCIAL-MICRO";"Fiducial Alignment Points";"";"";"";"";
"FD3";"FIDUCIALUFIDUCIAL";"FIDUCIALUFIDUCIAL";"FIDUCIAL-MICRO";"Fiducial Alignment Points";"";"";"";"";
"FD4";"FIDUCIALUFIDUCIAL";"FIDUCIALUFIDUCIAL";"FIDUCIAL-MICRO";"Fiducial Alignment Points";"";"";"";"";
"FRAME1";"FRAME-LETTER";"FRAME-LETTER";"CREATIVE_COMMONS";"Schematic Frame - Letter";"";"";"";"";
"H1";"STAND-OFFTIGHT";"STAND-OFFTIGHT";"STAND-OFF-TIGHT";"Stand Off";"";"";"";"";
"H2";"STAND-OFFTIGHT";"STAND-OFFTIGHT";"STAND-OFF-TIGHT";"Stand Off";"";"";"";"";
"J1";"QWIIC_RIGHT_ANGLE";"QWIIC_CONNECTORJS-1MM";"JST04_1MM_RA";"SparkFun I2C Standard Qwiic Connector";"";"CONN-13694";"";"QWIIC_RIGHT_ANGLE";
"J2";"QWIIC_RIGHT_ANGLE";"QWIIC_CONNECTORJS-1MM";"JST04_1MM_RA";"SparkFun I2C Standard Qwiic Connector";"";"CONN-13694";"";"QWIIC_RIGHT_ANGLE";
"J3";"QWIIC_RIGHT_ANGLE";"QWIIC_CONNECTORJS-1MM";"JST04_1MM_RA";"SparkFun I2C Standard Qwiic Connector";"";"CONN-13694";"";"QWIIC_RIGHT_ANGLE";
"J4";"QWIIC_RIGHT_ANGLE";"QWIIC_CONNECTORJS-1MM";"JST04_1MM_RA";"SparkFun I2C Standard Qwiic Connector";"";"CONN-13694";"";"QWIIC_RIGHT_ANGLE";
"JP1";"PWR_LED";"JUMPER-SMT_2_NC_TRACE_SILK";"SMT-JUMPER_2_NC_TRACE_SILK";"Normally closed trace jumper";"";"";"";"";
"LOGO1";"QWIIC_LOGO_5MM";"QWIIC_LOGO_5MM";"QWIIC_5MM";"Qwiic Logos for placement on schematic and PCB. The 5.5mm silk logo is best for placing next to Qwiic connector.";"";"";"";"";
"LOGO2";"QWIIC_LOGO_5MM";"QWIIC_LOGO_5MM";"QWIIC_5MM";"Qwiic Logos for placement on schematic and PCB. The 5.5mm silk logo is best for placing next to Qwiic connector.";"";"";"";"";
"LOGO3";"OSHW-LOGOS";"OSHW-LOGOS";"OSHW-LOGO-S";"Open-Source Hardware (OSHW) Logo";"";"";"";"";
"LOGO4";"SFE_LOGO_NAME.2_INCH";"SFE_LOGO_NAME.2_INCH";"SFE_LOGO_NAME_.2";"SparkFun Font Logo";"";"";"";"";
"R1";"1k";"1KOHM-0603-1/10W-1%";"0603";"1kΩ resistor";"";"RES-07856";"";"1k";

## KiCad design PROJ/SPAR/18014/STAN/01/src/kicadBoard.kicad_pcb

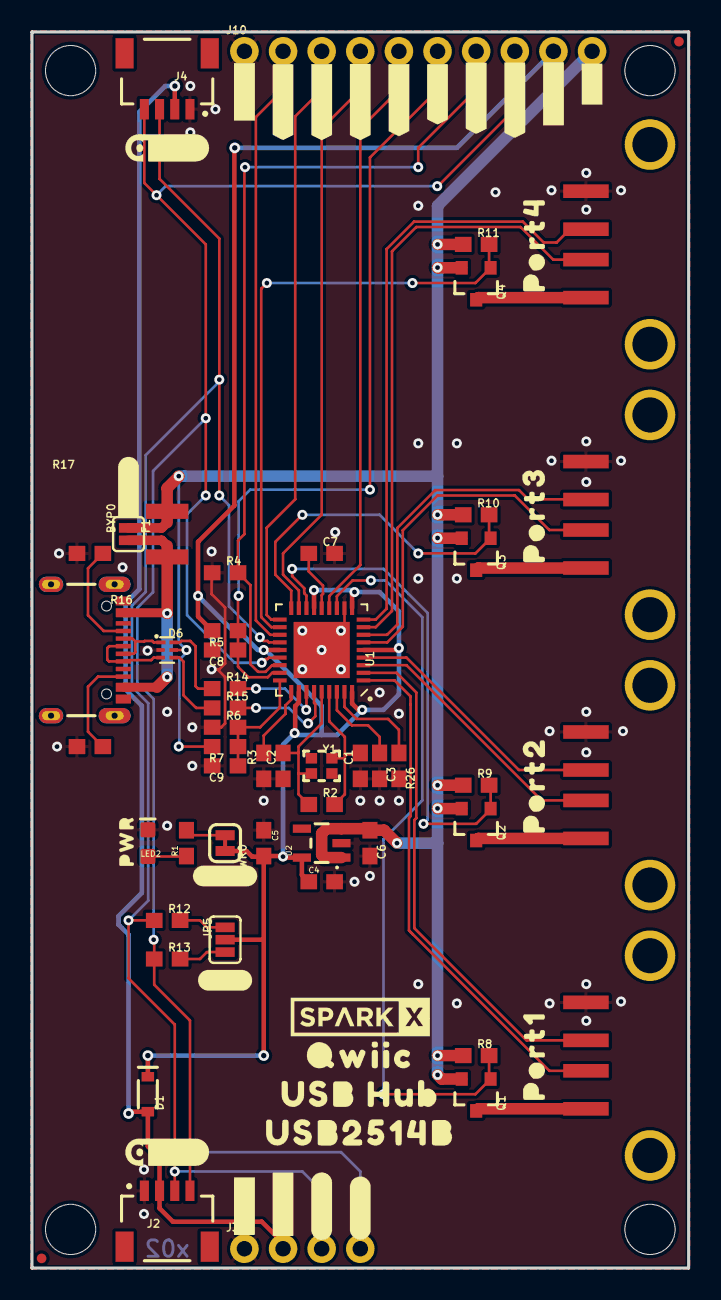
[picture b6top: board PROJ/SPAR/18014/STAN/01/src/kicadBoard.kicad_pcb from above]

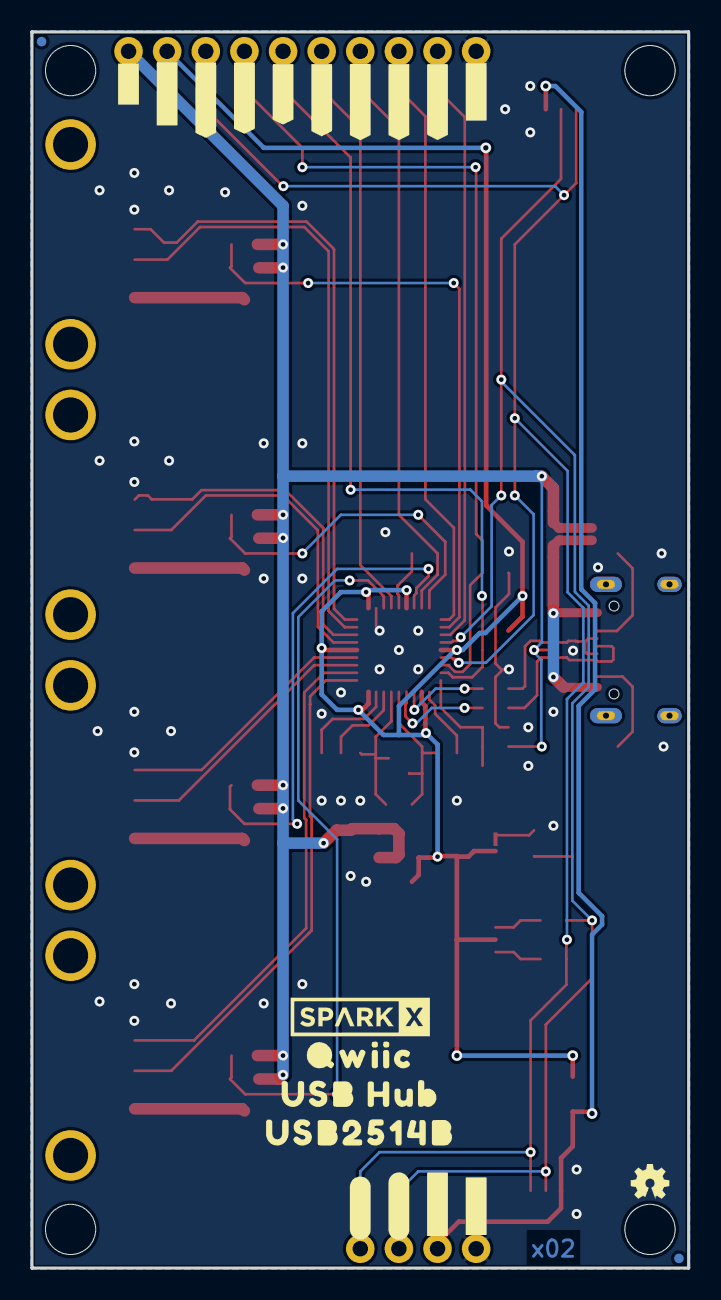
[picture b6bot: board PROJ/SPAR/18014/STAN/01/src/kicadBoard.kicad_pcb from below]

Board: 2 copper layers, 43.2 x 81.3 mm, 106 parts (21 on the bottom side), 48 nets.

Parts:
BYP0: JUMPER-SMT_2_NO_SILK; SMT-JUMPER_2_NO_SILK
C1, C2: 18pF; 0603
C3, C5, C7, C8, C9: 0.1uF; 0603
C4, C6: 1.0uF; 0603
D1: 3A/10V/280mV; SOD-323
D6: PRTR5V0U2F; SOT886
F1: 6V/2A; 1210
FRAME2: FRAME-LEDGER; CREATIVE_COMMONS
J1, J6, J8, J9: USB_A_FEMALE; USB-A-S-NOSILK-FEMALE
J2, J4: Qwiic Right Angle; JST04_1MM_RA
J3: PTH; 1X04_NO_SILK
J5: USB-C-16P-2LAYER-PADS
J10: 1X10_NO_SILK
JP5: SMT-JUMPER_3_NO_SILK
JP21, JP61, JP71, JP81: FIDUCIALUFIDUCIAL; MICRO-FIDUCIAL
JP31, JP41, JP91, JP101: STAND-OFF
LED2: RED; LED-0603
LOGO1: OSHW-LOGOMINI; OSHW-LOGO-MINI
LOGO2: QWIIC_LOGO_CONNECTOR; QWIIC_5.5MM
PWR0: SMT-JUMPER_2_NC_TRACE_SILK
Q1, Q2, Q3, Q4: 4.3A/20V/54mΩ; SOT23-3
R1: 1k; 0603
R2: 1M; 0603
R3, R4, R5, R6, R7, R8, R9, R10, R11: 100k; 0603
R12, R13: 2.2k; 0603
R14, R15: 22; 0603
R16, R17: 5.1k; 0603
R26: 12k; 0603
U1: USB251XB; QFN-36
U2: 3.3V; SOT23-5
U$1: PORT40
U$2: PORT31
U$3: PORT22
U$4: PORT13
U$5, U$38: SPARKX-LOGO4; SPARKX-MEDIUM
U$6, U$34: #3#3V#0
U$7, U$35: #SDA#0
U$8, U$36: #SCL#0
U$9, U$33: #GND#0
U$10: #I�C#1
U$11, U$16: #GND#5
U$12: PWR0
U$13, U$31: ##RST##4
U$14, U$32: #3#3V#6
U$15, U$37: #5V#7
U$17, U$30: ##OCS1##3
U$18, U$43: ##OCS2##2
U$19, U$44: ##OCS3##1
U$20, U$45: ##OCS4##0
U$21: #BYP#0
U$22, U$39: QWIIC2
U$23: #LED#0
U$24, U$29: #CFG0#1
U$25, U$28: #CFG1#0
U$26, U$41: USB2514B0
U$27, U$40: USB_HUB1
U$42: QWIIC_5.5MM
Y1: 24MHz; CRYSTAL-SMD-2.0X1.6MM

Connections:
3.3V: C4.1, C5.2, D1.C, J10.9, JP5.2, PWR0.2, R5.2, U1.5, U1.10, U1.15, U1.23, U1.29, U1.36, U2.5
5V: BYP0.2, C6.1, D6.5, F1.2, J10.10, Q1.2, Q2.2, Q3.2, Q4.2, R7.2, R8.1, R9.1, R10.1, R11.1, U2.1, U2.3
CC1: J5.A5, R17.2
CC2: J5.B5, R16.2
CFG1: J10.7, R4.2, U1.25
D_N: D6.6, R14.1
D_P: D6.4, R15.1
GND: C1.1, C2.1, C3.2, C4.2, C5.1, C6.2, C7.2, C8.2, C9.2, D6.2, J1.GND, J2.1, J3.1, J4.1, J5.GND, J5.GND2, J5.SHLD1, J5.SHLD2, J5.SHLD3, J5.SHLD4, J6.GND, J8.GND, J9.GND, J10.1, LED2.C, R3.1, R4.1, R6.1, R16.1, R17.1, R26.2, U1.11, U1.EP, U2.2
unnamed: J1.VBUS, Q1.3
unnamed: J6.VBUS, Q2.3
unnamed: J8.VBUS, Q3.3
unnamed: J9.VBUS, Q4.3
unnamed: R26.1, U1.35
unnamed: C1.2, R2.2, U1.33, Y1.3
unnamed: BYP0.1, F1.1, J5.VBUS1, J5.VBUS2
unnamed: C2.2, R2.1, U1.32, Y1.1
unnamed: JP5.1, R13.2
unnamed: LED2.A, R1.1
unnamed: R3.2, U1.28
unnamed: C3.1, U1.34
unnamed: C7.1, U1.14
unnamed: JP5.3, R12.2
unnamed: R14.2, U1.30
unnamed: PWR0.1, R1.2
unnamed: R15.2, U1.31
unnamed: D1.A, J2.2, J3.2, J4.2
PORT1_N: J1.D-, U1.1
PORT1_P: J1.D+, U1.2
PORT2_N: J6.D-, U1.3
PORT2_P: J6.D+, U1.4
PORT3_N: J8.D-, U1.6
PORT3_P: J8.D+, U1.7
PORT4_N: J9.D-, U1.8
PORT4_P: J9.D+, U1.9
PRTPWR1: Q1.1, R8.2, U1.12
PRTPWR2: Q2.1, R9.2, U1.16
PRTPWR3: Q3.1, R10.2, U1.18
PRTPWR4: Q4.1, R11.2, U1.20
SCL/CFG0: J2.4, J3.4, J4.4, J10.8, R13.1, U1.24
SDA: J2.3, J3.3, J4.3, R12.1, U1.22
UNP_D+: D6.3, J5.A6, J5.B6
UNP_D-: D6.1, J5.A7, J5.B7
VBUS_DET: C9.1, R6.2, R7.1, U1.27
~OCS1: J10.5, U1.13
~OCS2: J10.4, U1.17
~OCS3: J10.3, U1.19
~OCS4: J10.2, U1.21
~RESET: C8.1, J10.6, R5.1, U1.26

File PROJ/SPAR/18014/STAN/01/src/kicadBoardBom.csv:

"Id";"Designator";"Package";"Quantity";"Designation";"Supplier and ref";
1;"C9,C5,C7,C3,C8";"0603";5;"0.1uF";;;
2;"R15,R14";"0603";2;"22";;;
3;"FRAME2";"CREATIVE_COMMONS";1;"FRAME-LEDGER";;;
4;"JP5";"SMT-JUMPER_3_NO_SILK";1;"";;;
5;"R17,R16";"0603";2;"5.1k";;;
6;"J6,J8,J9,J1";"USB-A-S-NOSILK-FEMALE";4;"USB_A_FEMALE";;;
7;"U$36,U$8";"#SCL#0";2;"";;;
8;"LOGO2";"QWIIC_5.5MM";1;"QWIIC_LOGO_CONNECTOR";;;
9;"JP41,JP31,JP91,JP101";"STAND-OFF";4;"STAND-OFF";;;
10;"U$24,U$29";"#CFG0#1";2;"";;;
11;"D6";"SOT886";1;"PRTR5V0U2F";;;
12;"D1";"SOD-323";1;"3A/10V/280mV";;;
13;"C2,C1";"0603";2;"18pF";;;
14;"U$18,U$43";"##OCS2##2";2;"";;;
15;"R10,R8,R9,R7,R6,R11,R3,R5,R4";"0603";9;"100k";;;
16;"J10";"1X10_NO_SILK";1;"";;;
17;"U$27,U$40";"USB_HUB1";2;"";;;
18;"U$14,U$32";"#3#3V#6";2;"";;;
19;"U$35,U$7";"#SDA#0";2;"";;;
20;"LED2";"LED-0603";1;"RED";;;
21;"U$16,U$11";"#GND#5";2;"";;;
22;"R1";"0603";1;"1k";;;
23;"J3";"1X04_NO_SILK";1;"PTH";;;
24;"U$5,U$38";"SPARKX-MEDIUM";2;"SPARKX-LOGO4";;;
25;"U$22,U$39";"QWIIC2";2;"";;;
26;"U$25,U$28";"#CFG1#0";2;"";;;
27;"U$13,U$31";"##RST##4";2;"";;;
28;"Y1";"CRYSTAL-SMD-2.0X1.6MM";1;"24MHz";;;
29;"U$10";"#I�C#1";1;"";;;
30;"J4,J2";"JST04_1MM_RA";2;"Qwiic Right Angle";;;
31;"Q3,Q2,Q4,Q1";"SOT23-3";4;"4.3A/20V/54mΩ";;;
32;"R12,R13";"0603";2;"2.2k";;;
33;"PWR0";"SMT-JUMPER_2_NC_TRACE_SILK";1;"";;;
34;"U$23";"#LED#0";1;"";;;
35;"R26";"0603";1;"12k";;;
36;"U$34,U$6";"#3#3V#0";2;"";;;
37;"U$42";"QWIIC_5.5MM";1;"";;;
38;"U$20,U$45";"##OCS4##0";2;"";;;
39;"U$15,U$37";"#5V#7";2;"";;;
40;"C6,C4";"0603";2;"1.0uF";;;
41;"U$26,U$41";"USB2514B0";2;"";;;
42;"BYP0";"SMT-JUMPER_2_NO_SILK";1;"JUMPER-SMT_2_NO_SILK";;;
43;"U$1";"PORT40";1;"";;;
44;"JP21,JP61,JP81,JP71";"MICRO-FIDUCIAL";4;"FIDUCIALUFIDUCIAL";;;
45;"U$2";"PORT31";1;"";;;
46;"U$17,U$30";"##OCS1##3";2;"";;;
47;"U$12";"PWR0";1;"";;;
48;"R2";"0603";1;"1M";;;
49;"U1";"QFN-36";1;"USB251XB";;;
50;"U$3";"PORT22";1;"";;;
51;"U$19,U$44";"##OCS3##1";2;"";;;
52;"U2";"SOT23-5";1;"3.3V";;;
53;"U$4";"PORT13";1;"";;;
54;"J5";"USB-C-16P-2LAYER-PADS";1;"";;;
55;"U$33,U$9";"#GND#0";2;"";;;
56;"U$21";"#BYP#0";1;"";;;
57;"F1";"1210";1;"6V/2A";;;
58;"LOGO1";"OSHW-LOGO-MINI";1;"OSHW-LOGOMINI";;;

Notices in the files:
parts and their libraries:
HTTPS://CREATIVECOMMONS.ORG/LICENSES/BY-SA/4.0
RELEASED UNDER THE CREATIVE COMMONS ATTRIBUTION SHARE-ALIKE 4.0 LICENSE
